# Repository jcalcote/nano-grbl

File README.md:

# nano-grbl
A KiCAD circuit board for embedding an Arduino Nano V3 and breaking out the I/O pins for GRBL.

This KiCAD project is a simple pcb allowing the embedding of an entire Arduino Nano along side minimal additional hardware for breaking out and labling I/O pins for the [GRBL](https://github.com/gnea/grbl) gcode interpreter software package.

## 3D Model

## Requirements

To use this KiCAD project, you should also clone my KiCAD parts library and add it to your clone of this project. See <https://github.com/jcalcote/KiCAD-footprints>.

## License

Creative Commons Zero 1.0 - Use at will and please enjoy.

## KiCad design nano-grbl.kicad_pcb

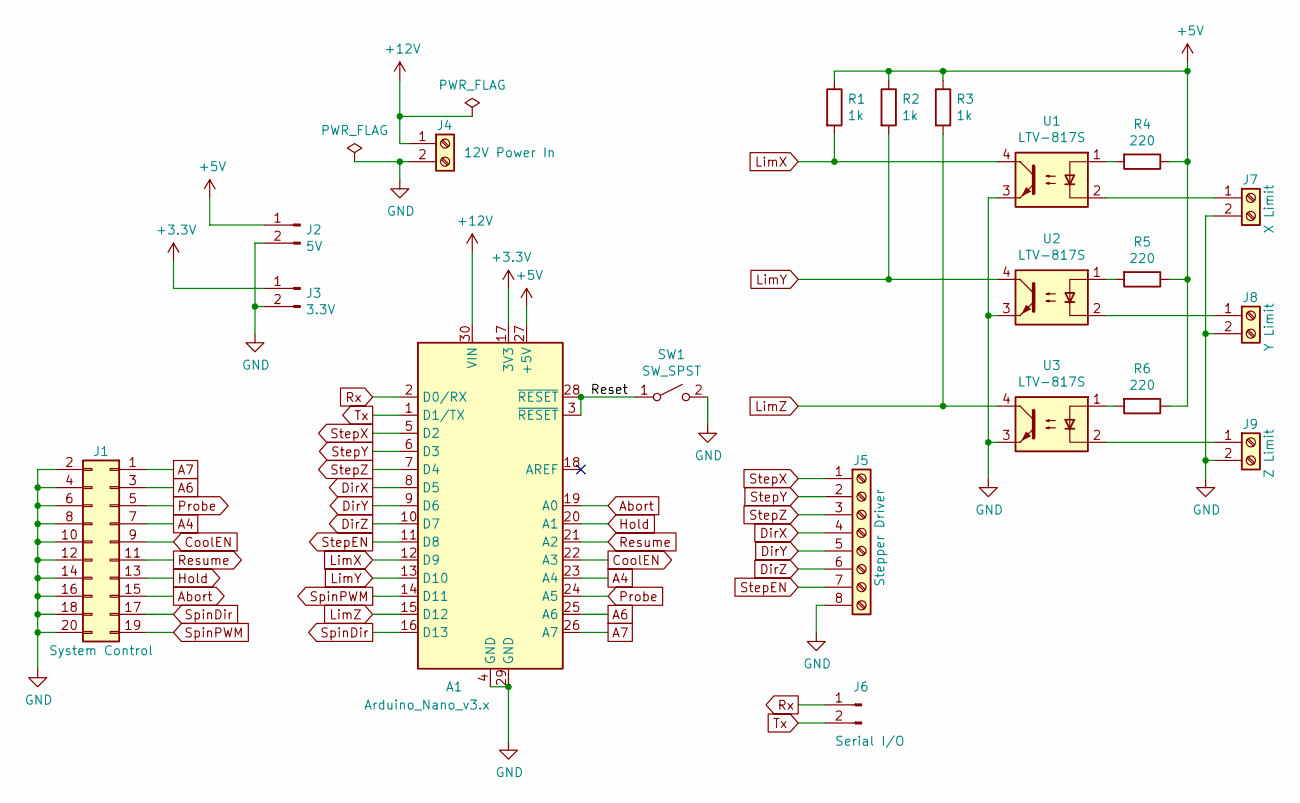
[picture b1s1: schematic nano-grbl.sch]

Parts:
A1: Arduino_Nano_v3.x; Arduino_Nano
J1: System Control; PinHeader_2x10_P2.54mm_Vertical
J2: 5V; PinHeader_1x02_P2.54mm_Vertical
J3: 3.3V; PinHeader_1x02_P2.54mm_Vertical
J4: 12V Power In; TerminalBlock_Phoenix_PT-1,5-2-3.5-H_1x02_P3.50mm_Horizontal
J5: Stepper Driver; TerminalBlock_Phoenix_PT-1,5-8-3.5-H_1x08_P3.50mm_Horizontal
J6: Serial I/O; PinHeader_1x02_P2.54mm_Vertical
J7: X Limit; TerminalBlock_Phoenix_PT-1,5-2-3.5-H_1x02_P3.50mm_Horizontal
J8: Y Limit; TerminalBlock_Phoenix_PT-1,5-2-3.5-H_1x02_P3.50mm_Horizontal
J9: Z Limit; TerminalBlock_Phoenix_PT-1,5-2-3.5-H_1x02_P3.50mm_Horizontal
R1, R2, R3: 1k; R_0805_2012Metric_Pad1.20x1.40mm_HandSolder
R4, R5, R6: 220; R_0805_2012Metric_Pad1.20x1.40mm_HandSolder
SW1: SW_SPST; SW_SPST_MOMENTARY_3x6_SMD
U1, U2, U3: LTV-817S; SMDIP-4_W9.53mm

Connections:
+3V3: A1.17 (3V3), J3.1
+5V: A1.27 (+5V), J2.1, R1.1, R2.1, R3.1, R4.1, R5.1, R6.1
+12V: A1.30 (VIN), J4.1
/Reset: A1.3 (~RESET), A1.28 (~RESET), SW1.1 (A)
A4: A1.23 (A4), J1.7
A6: A1.25 (A6), J1.3
A7: A1.26 (A7), J1.1
Abort: A1.19 (A0), J1.15
CoolEN: A1.22 (A3), J1.9
DirX: A1.8 (D5), J5.4
DirY: A1.9 (D6), J5.5
DirZ: A1.10 (D7), J5.6
GND: A1.4 (GND), A1.29 (GND), J1.2, J1.4, J1.6, J1.8, J1.10, J1.12, J1.14, J1.16, J1.18, J1.20, J2.2, J3.2, J4.2, J5.8, J7.2, J8.2, J9.2, SW1.2 (B), U1.3, U2.3, U3.3
Hold: A1.20 (A1), J1.13
LimX: A1.12 (D9), R1.2, U1.4
LimY: A1.13 (D10), R2.2, U2.4
LimZ: A1.15 (D12), R3.2, U3.4
unnamed: J7.1, U1.2
unnamed: J8.1, U2.2
unnamed: J9.1, U3.2
unnamed: R4.2, U1.1
unnamed: R5.2, U2.1
unnamed: R6.2, U3.1
Probe: A1.24 (A5), J1.5
Resume: A1.21 (A2), J1.11
Rx: A1.2 (D0/RX), J6.1
SpinDir: A1.16 (D13), J1.17
SpinPWM: A1.14 (D11), J1.19
StepEN: A1.11 (D8), J5.7
StepX: A1.5 (D2), J5.1
StepY: A1.6 (D3), J5.2
StepZ: A1.7 (D4), J5.3
Tx: A1.1 (D1/TX), J6.2

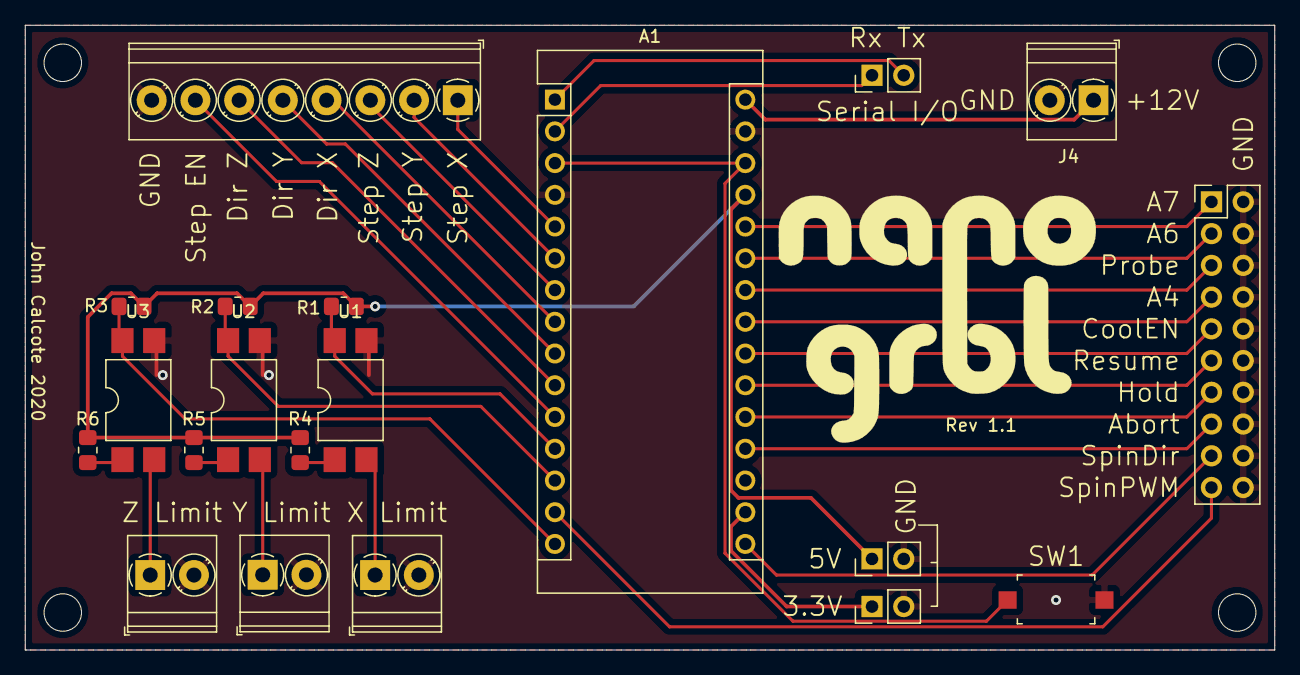
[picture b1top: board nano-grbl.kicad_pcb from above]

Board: 2 copper layers, 100.0 x 50.0 mm, 20 parts (0 on the bottom side), 33 nets.

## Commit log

2020-12-21 Initial commit of board revision 1.1
2020-12-22 Update README and pcb for new footprint location.
2020-12-22 Fix link mistake in README.md.
